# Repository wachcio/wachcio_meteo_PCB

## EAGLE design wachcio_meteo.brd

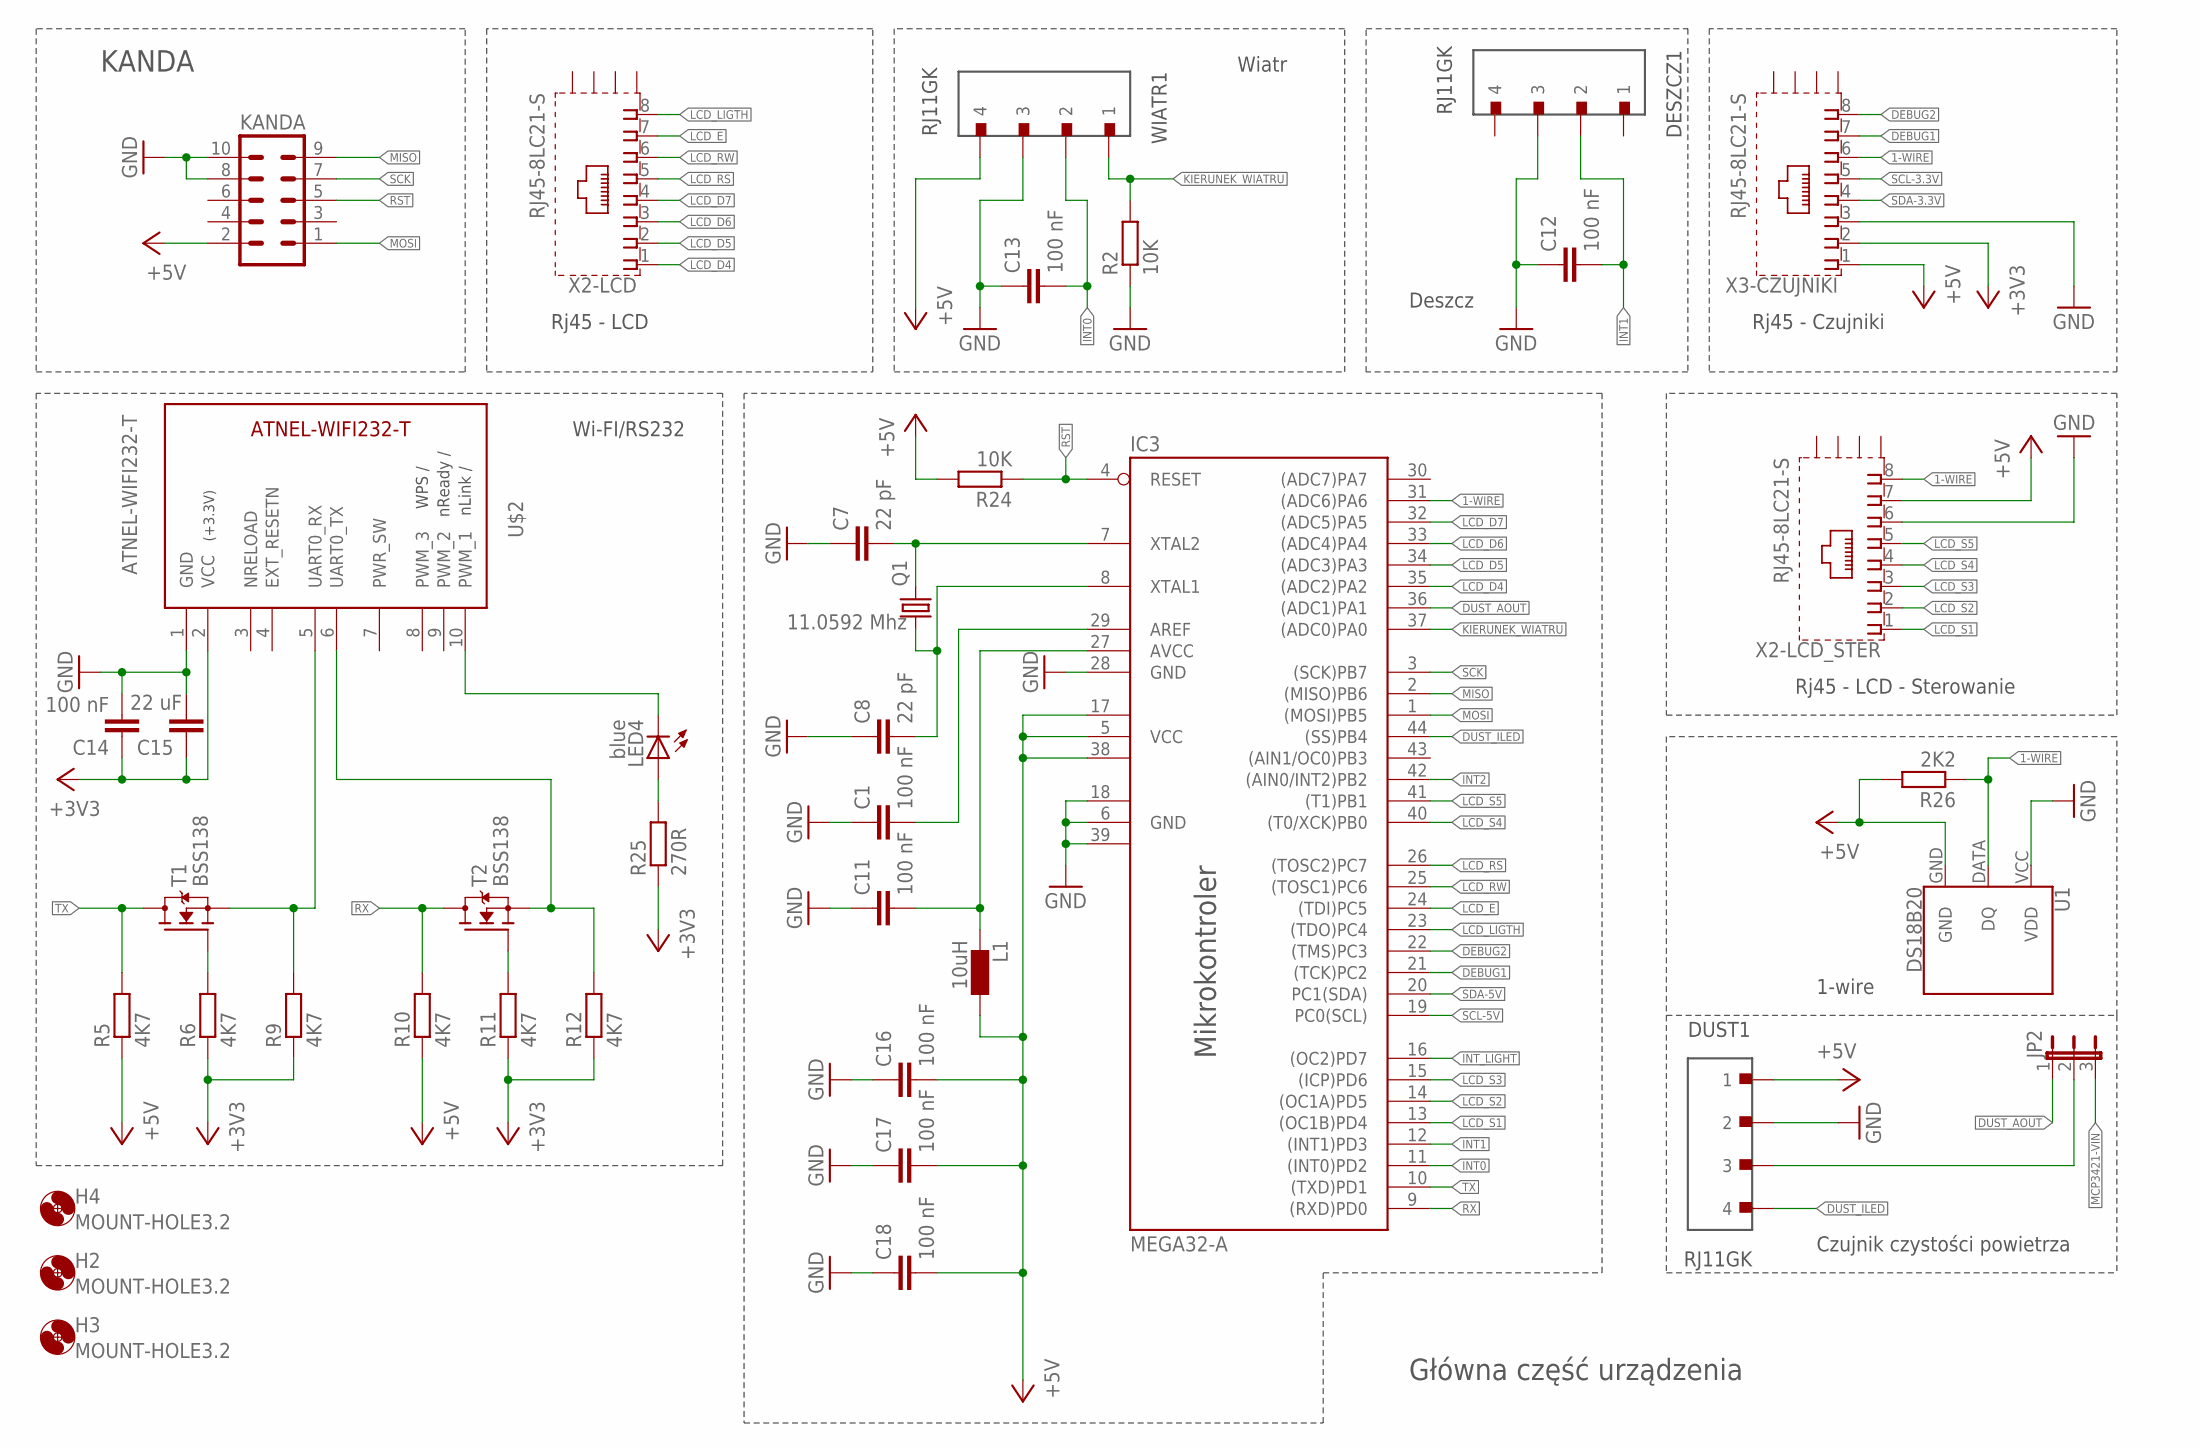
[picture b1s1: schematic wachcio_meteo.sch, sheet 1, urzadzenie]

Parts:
C1, C11, C12, C13, C14, C16, C17, C18: 100 nF; C0805
C7, C8: 22 pF; C0805
C15: 22 uF; C0805
DESZCZ1: RJ11GK
DUST1: RJ11GK
H2, H3, H4: MOUNT-HOLE3.2; 3,2
IC3: MEGA32-A; TQFP44
JP2: JP2E; JP2
KANDA: ML10
L1: 10uH; L3230M
LED4: blue; CHIPLED_1206
Q1: 11.0592 Mhz; SM49
R2, R24: 10K; M0805
R5, R6, R9, R10, R11, R12: 4K7; M0805
R25: 270R; M0805
R26: 2K2; M0805
T1, T2: BSS138; SOT23
U1: DS18B20; TO-92-AMMO
U$2: ATNEL-WIFI232-T
WIATR1: RJ11GK
X2-LCD, X2-LCD_STER, X3-CZUJNIKI: RJ45-8LC21-S; RJ45-SHIELD1

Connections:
1-WIRE: IC3.31 ((ADC6)PA6), R26.1, U1.DATA (DQ), X2-LCD_STER.8, X3-CZUJNIKI.6
+3V3: C14.1, C15.1, R6.1, R9.1, R11.1, R12.1, R25.1, U$2.2 (VCC), X3-CZUJNIKI.2; also elsewhere on the board
+5V: C16.2, C17.2, C18.2, DUST1.1, IC3.5 (VCC), IC3.17 (VCC1), IC3.38 (VCC2), KANDA.2, L1.1, R5.1, R10.1, R24.2, R26.2, U1.GND, WIATR1.4, X2-LCD_STER.7, X3-CZUJNIKI.1; also elsewhere on the board
DEBUG1: IC3.21 ((TCK)PC2), X3-CZUJNIKI.7; also elsewhere on the board
DEBUG2: IC3.22 ((TMS)PC3), X3-CZUJNIKI.8; also elsewhere on the board
DUST_AOUT: IC3.36 ((ADC1)PA1), JP2.1
DUST_ILED: DUST1.4, IC3.44 ((SS)PB4)
GND: C1.1, C7.1, C8.1, C11.1, C12.1, C13.1, C14.2, C15.2, C16.1, C17.1, C18.1, DESZCZ1.3, DUST1.2, IC3.6 (GND), IC3.18 (GND1), IC3.28 (GND), IC3.39 (GND2), KANDA.8, KANDA.10, R2.1, U1.VCC (VDD), U$2.1 (GND), WIATR1.3, X2-LCD_STER.6, X3-CZUJNIKI.3; also elsewhere on the board
INT0: C13.2, IC3.11 ((INT0)PD2), WIATR1.2
INT1: C12.2, DESZCZ1.2, IC3.12 ((INT1)PD3)
INT2: IC3.42 ((AIN0/INT2)PB2); also elsewhere on the board
INT_LIGHT: IC3.16 ((OC2)PD7); also elsewhere on the board
KIERUNEK_WIATRU: IC3.37 ((ADC0)PA0), R2.2, WIATR1.1
LCD_D4: IC3.35 ((ADC2)PA2), X2-LCD.1
LCD_D5: IC3.34 ((ADC3)PA3), X2-LCD.2
LCD_D6: IC3.33 ((ADC4)PA4), X2-LCD.3
LCD_D7: IC3.32 ((ADC5)PA5), X2-LCD.4
LCD_E: IC3.24 ((TDI)PC5), X2-LCD.7
LCD_LIGTH: IC3.23 ((TDO)PC4), X2-LCD.8
LCD_RS: IC3.26 ((TOSC2)PC7), X2-LCD.5
LCD_RW: IC3.25 ((TOSC1)PC6), X2-LCD.6
LCD_S1: IC3.13 ((OC1B)PD4), X2-LCD_STER.1
LCD_S2: IC3.14 ((OC1A)PD5), X2-LCD_STER.2
LCD_S3: IC3.15 ((ICP)PD6), X2-LCD_STER.3
LCD_S4: IC3.40 ((T0/XCK)PB0), X2-LCD_STER.4
LCD_S5: IC3.41 ((T1)PB1), X2-LCD_STER.5
MCP3421-VIN: JP2.3; also elsewhere on the board
MISO: IC3.2 ((MISO)PB6), KANDA.9
MOSI: IC3.1 ((MOSI)PB5), KANDA.1
unnamed: R9.2, T1.2 (S), U$2.5 (UART0_RX)
unnamed: C11.2, IC3.27 (AVCC), L1.2
unnamed: C1.2, IC3.29 (AREF)
unnamed: LED4.A, R25.2
unnamed: R6.2, T1.1 (G)
unnamed: LED4.C, U$2.10 (PWM_1)
unnamed: R12.2, T2.2 (S), U$2.6 (UART0_TX)
unnamed: C7.2, IC3.7 (XTAL2), Q1.2
unnamed: C8.2, IC3.8 (XTAL1), Q1.1
unnamed: DUST1.3, JP2.2
unnamed: R11.2, T2.1 (G)
RST: IC3.4 (RESET), KANDA.5, R24.1
RX: IC3.9 ((RXD)PD0), R10.2, T2.3 (D)
SCK: IC3.3 ((SCK)PB7), KANDA.7
SCL-3.3V: X3-CZUJNIKI.5; also elsewhere on the board
SCL-5V: IC3.19 (PC0(SCL)); also elsewhere on the board
SDA-3.3V: X3-CZUJNIKI.4; also elsewhere on the board
SDA-5V: IC3.20 (PC1(SDA)); also elsewhere on the board
TX: IC3.10 ((TXD)PD1), R5.2, T1.3 (D)

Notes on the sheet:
KANDA
Mikrokontroler
Rj45 - LCD
Wiatr
Deszcz
Rj45 - Czujniki
Wi-FI/RS232
1-wire
Rj45 - LCD - Sterowanie
Główna część urządzenia
Czujnik czystości powietrza

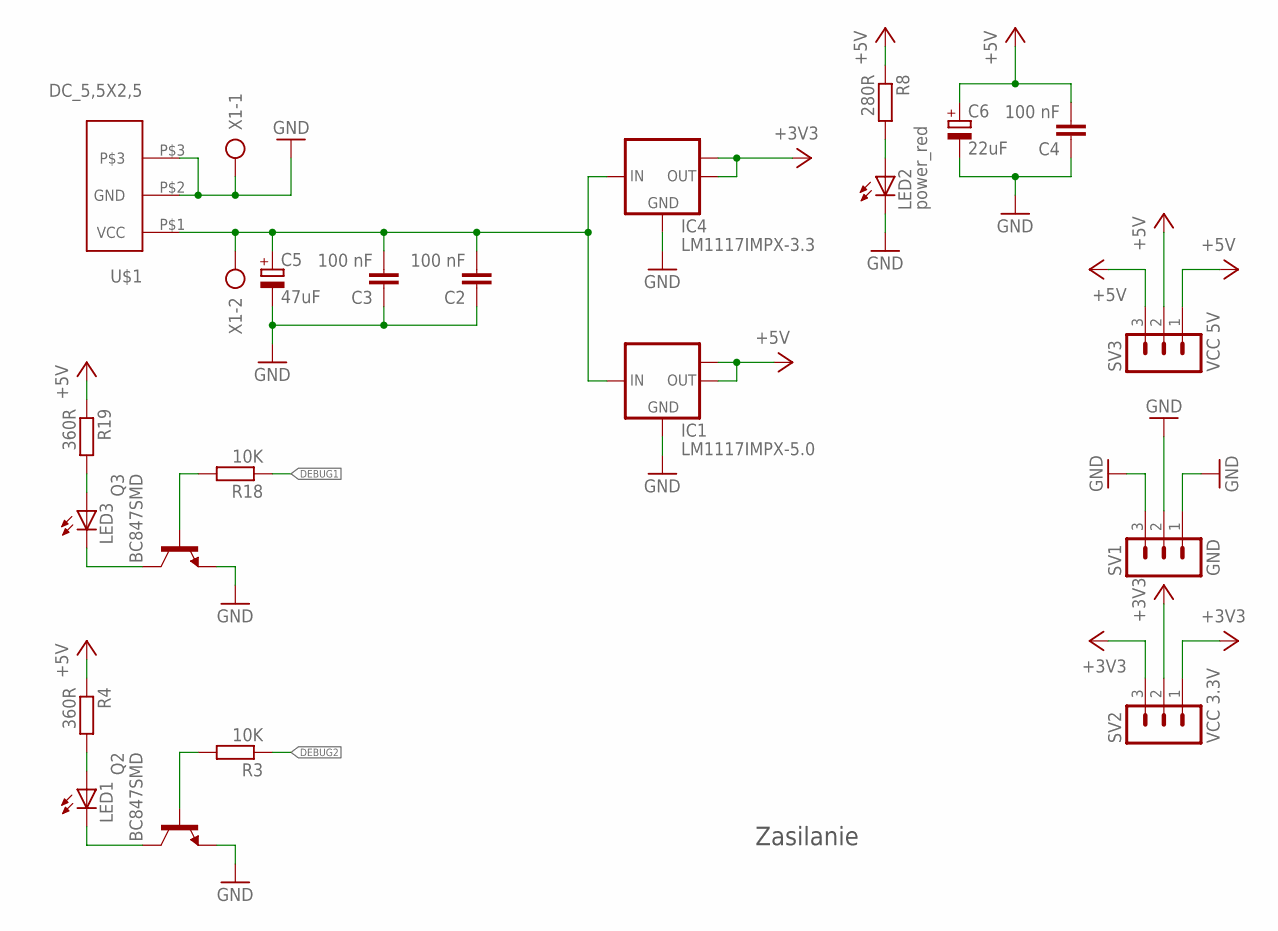
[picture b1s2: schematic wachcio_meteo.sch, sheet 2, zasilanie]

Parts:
C2, C3, C4: 100 nF; C0805
C5: 47uF; B45181A
C6: 22uF; B45181A
IC1: LM1117IMPX-5.0; SOT223
IC4: LM1117IMPX-3.3; SOT223
LED1, LED3: LED3MM
LED2: power_red; CHIPLED_1206
Q2, Q3: BC847SMD; SOT23
R3, R18: 10K; M0805
R4, R19: 360R; M0805
R8: 280R; M0805
SV1: GND; MA03-1
SV2: VCC 3.3V; MA03-1
SV3: VCC 5V; MA03-1
U$1: DC_5,5X2,5
X1: AK500/2

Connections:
+3V3: IC4.2 (OUT), IC4.TAB (OUT1), SV2.1, SV2.2, SV2.3; also elsewhere on the board
+5V: C4.2, C6.+, IC1.2 (OUT), IC1.TAB (OUT1), R4.1, R8.1, R19.1, SV3.1, SV3.2, SV3.3; also elsewhere on the board
+9V: C2.2, C3.2, C5.+, IC1.3 (IN), IC4.3 (IN), U$1.P$1 (VCC), X1.2
DEBUG1: R18.1; also elsewhere on the board
DEBUG2: R3.1; also elsewhere on the board
GND: C2.1, C3.1, C4.1, C5.-, C6.-, IC1.1 (GND), IC4.1 (GND), LED2.C, Q2.2 (E), Q3.2 (E), SV1.1, SV1.2, SV1.3, U$1.P$2 (GND), U$1.P$3, X1.1; also elsewhere on the board
unnamed: Q2.1 (B), R3.2
unnamed: LED2.A, R8.2
unnamed: LED1.K (C), Q2.3 (C)
unnamed: LED1.A, R4.2
unnamed: Q3.1 (B), R18.2
unnamed: LED3.K (C), Q3.3 (C)
unnamed: LED3.A, R19.2

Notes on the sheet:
Zasilanie

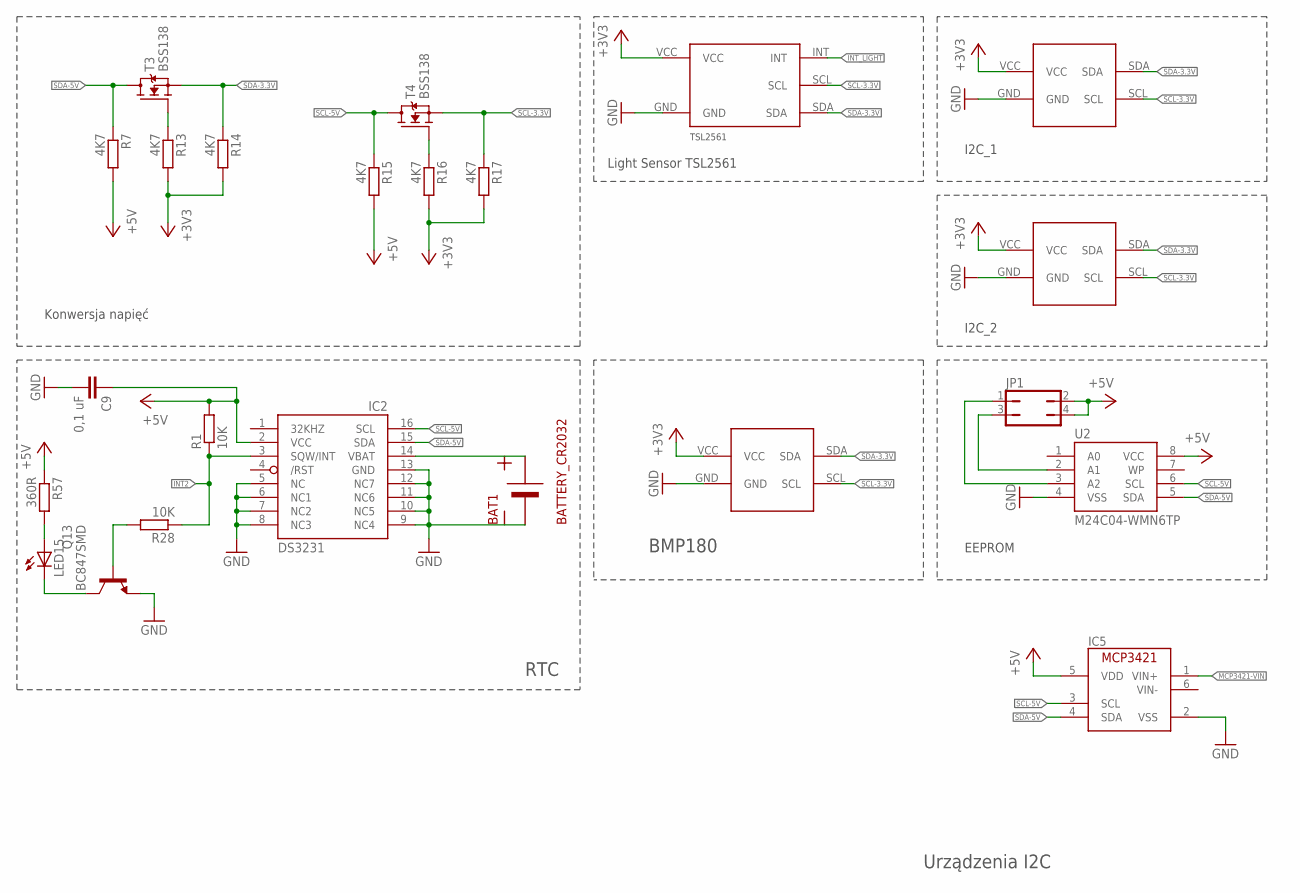
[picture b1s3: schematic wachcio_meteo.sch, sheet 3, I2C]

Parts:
BAT1: BATTERY_CR2032
C9: 0,1 uF; C0805
IC2: DS3231/SO; SO16W
IC5: MCP3421; SOT-23
JP1: JP2Q
LED15: LED3MM
Q13: BC847SMD; SOT23
R1, R28: 10K; M0805
R7, R13, R14, R15, R16, R17: 4K7; M0805
R57: 360R; M0805
T3, T4: BSS138; SOT23
U2: M24C04-WMN6TP; SO08
U$3: BMP180
U$5, U$6: I2C_BOARD
U$7: TSL2561GY-2561; TSL2561

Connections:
+3V3: R13.2, R14.2, R16.2, R17.2, U$3.VCC, U$5.VCC, U$6.VCC, U$7.VCC; also elsewhere on the board
+5V: C9.1, IC2.2 (VCC), IC5.5 (VDD), JP1.2, JP1.4, R1.2, R7.2, R15.2, R57.1, U2.8 (VCC); also elsewhere on the board
GND: BAT1.-, C9.2, IC2.5 (NC), IC2.6 (NC1), IC2.7 (NC2), IC2.8 (NC3), IC2.9 (NC4), IC2.10 (NC5), IC2.11 (NC6), IC2.12 (NC7), IC2.13 (GND), IC5.2 (VSS), Q13.2 (E), U2.4 (VSS), U$3.GND, U$5.GND, U$6.GND, U$7.GND; also elsewhere on the board
INT2: IC2.3 (SQW/INT), R1.1, R28.1; also elsewhere on the board
INT_LIGHT: U$7.INT; also elsewhere on the board
MCP3421-VIN: IC5.1 (VIN+); also elsewhere on the board
unnamed: BAT1.+, IC2.14 (VBAT)
unnamed: R13.1, T3.1 (G)
unnamed: R16.1, T4.1 (G)
unnamed: JP1.3, U2.2 (A1)
unnamed: JP1.1, U2.3 (A2)
unnamed: Q13.1 (B), R28.2
unnamed: LED15.K (C), Q13.3 (C)
unnamed: LED15.A, R57.2
SCL-3.3V: R17.1, T4.2 (S), U$3.SCL, U$5.SCL, U$6.SCL, U$7.SCL; also elsewhere on the board
SCL-5V: IC2.16 (SCL), IC5.3 (SCL), R15.1, T4.3 (D), U2.6 (SCL); also elsewhere on the board
SDA-3.3V: R14.1, T3.2 (S), U$3.SDA, U$5.SDA, U$6.SDA, U$7.SDA; also elsewhere on the board
SDA-5V: IC2.15 (SDA), IC5.4 (SDA), R7.1, T3.3 (D), U2.5 (SDA); also elsewhere on the board

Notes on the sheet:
Konwersja napięć
RTC
BMP180
I2C_1
I2C_2
EEPROM
Light Sensor TSL2561
Urządzenia I2C

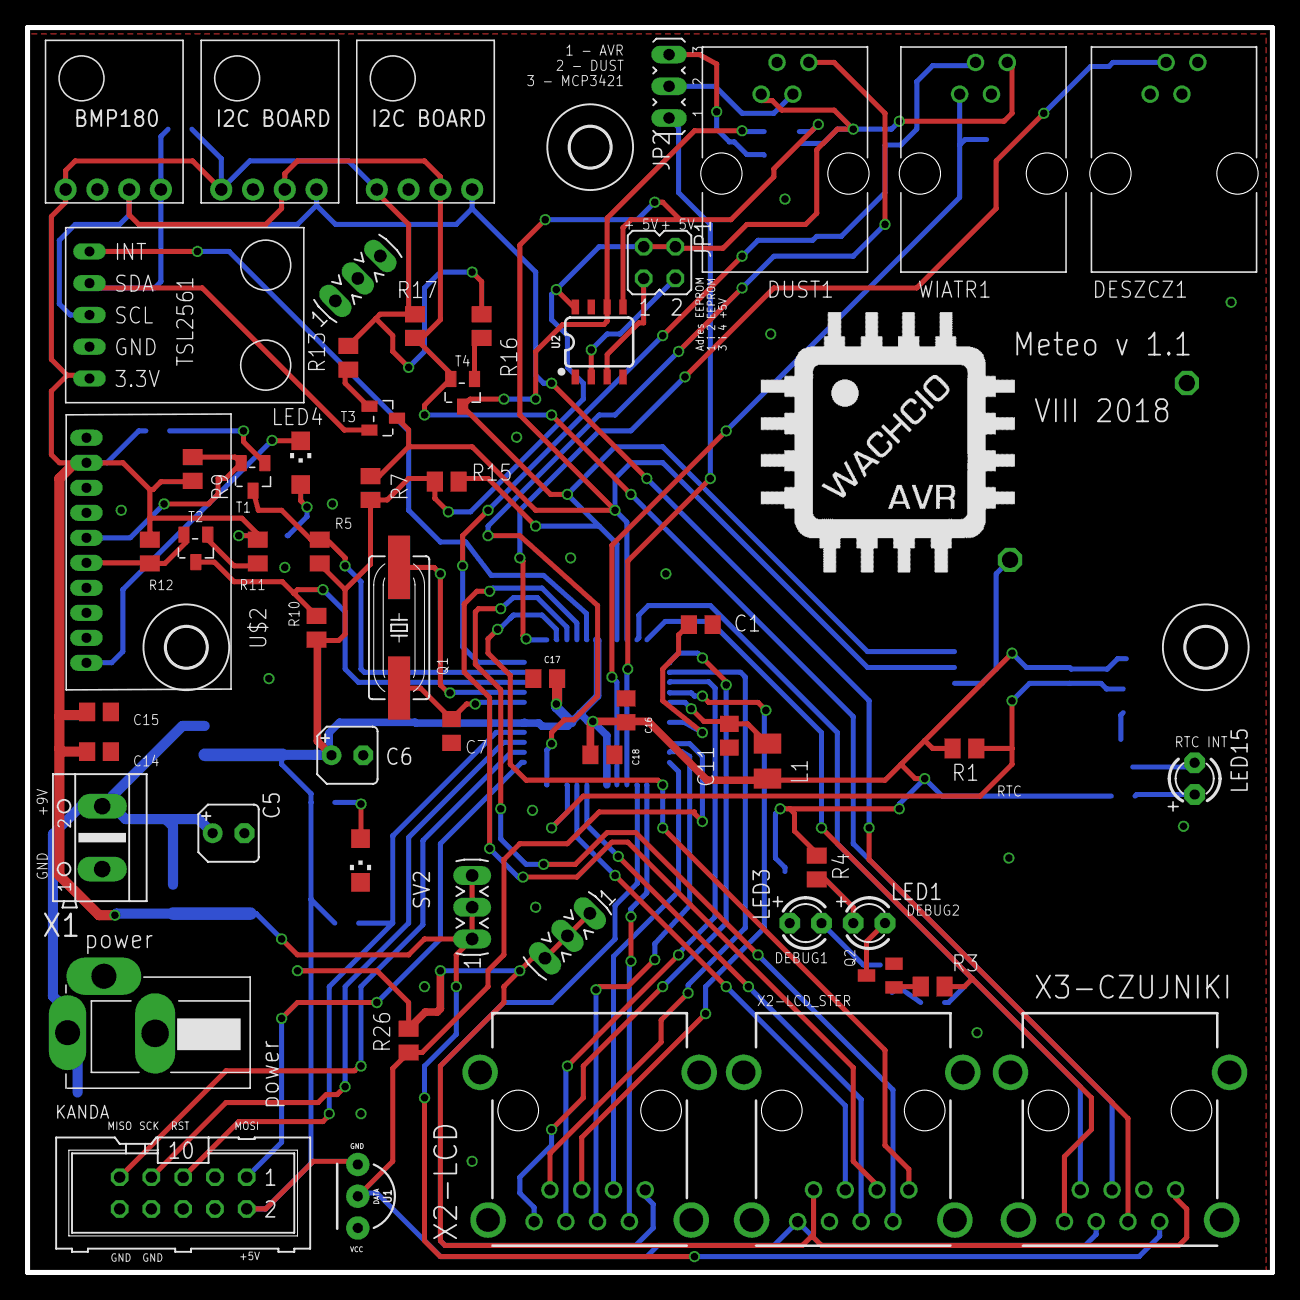
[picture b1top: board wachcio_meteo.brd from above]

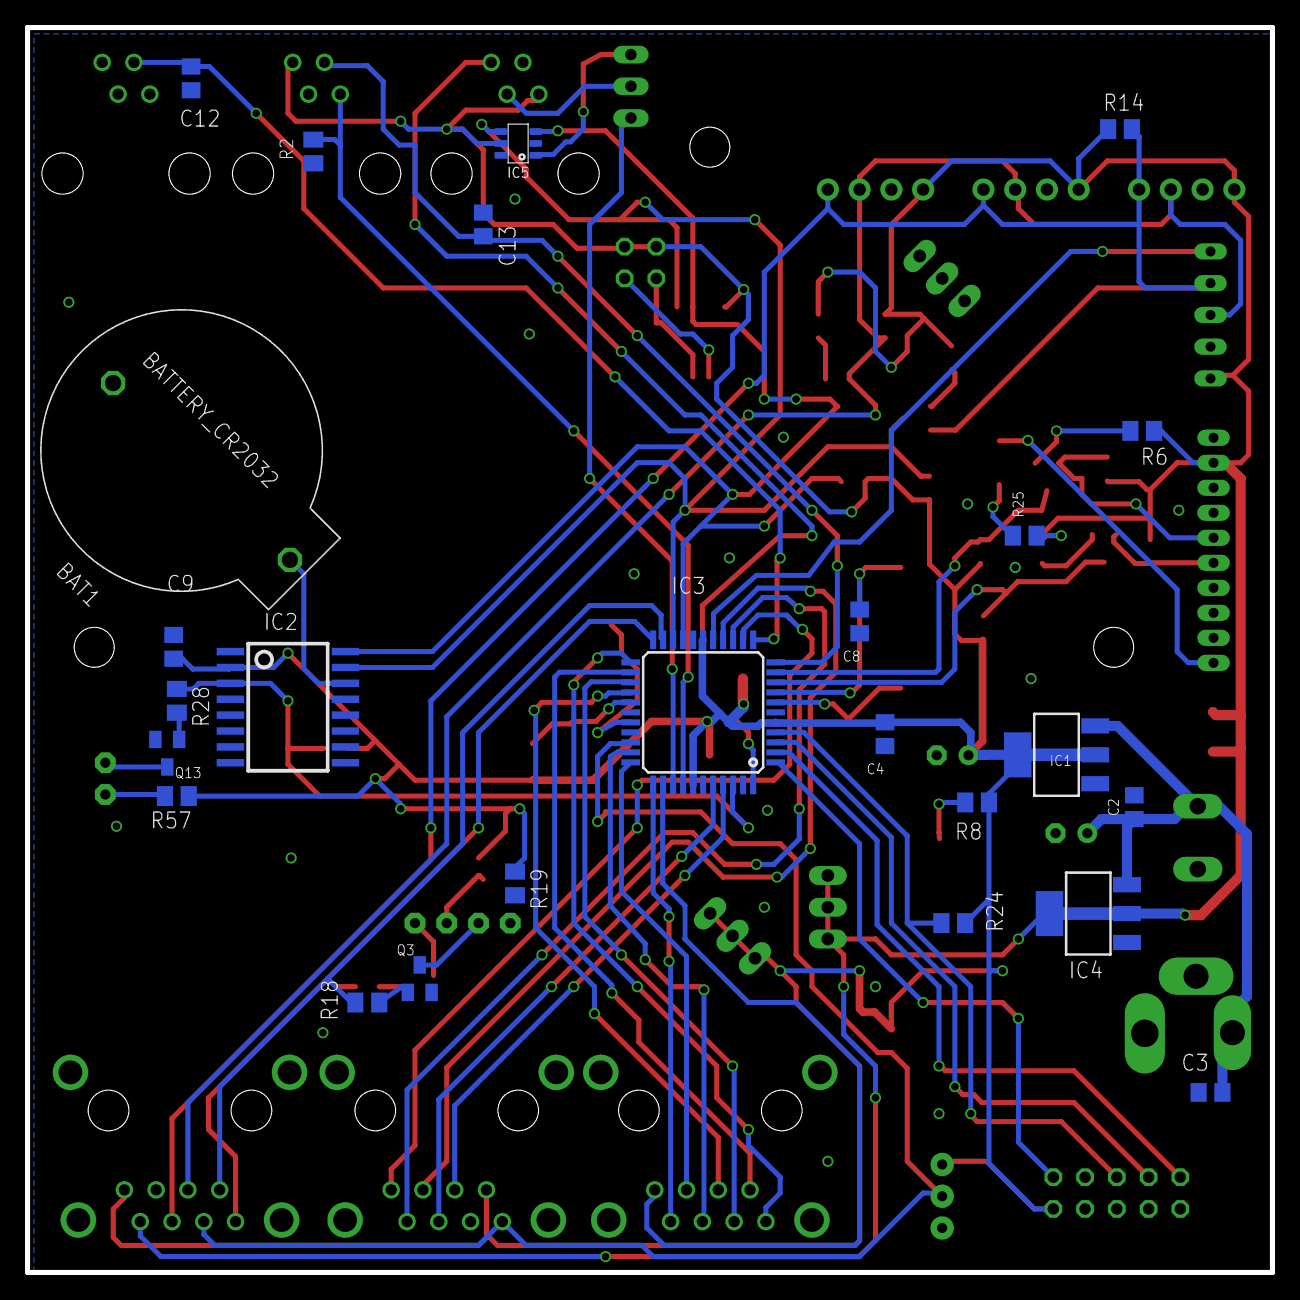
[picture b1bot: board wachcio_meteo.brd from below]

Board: 2 copper layers, 99.6 x 99.6 mm, 86 parts (25 on the bottom side), 64 nets.

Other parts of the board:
U$8: LOGO

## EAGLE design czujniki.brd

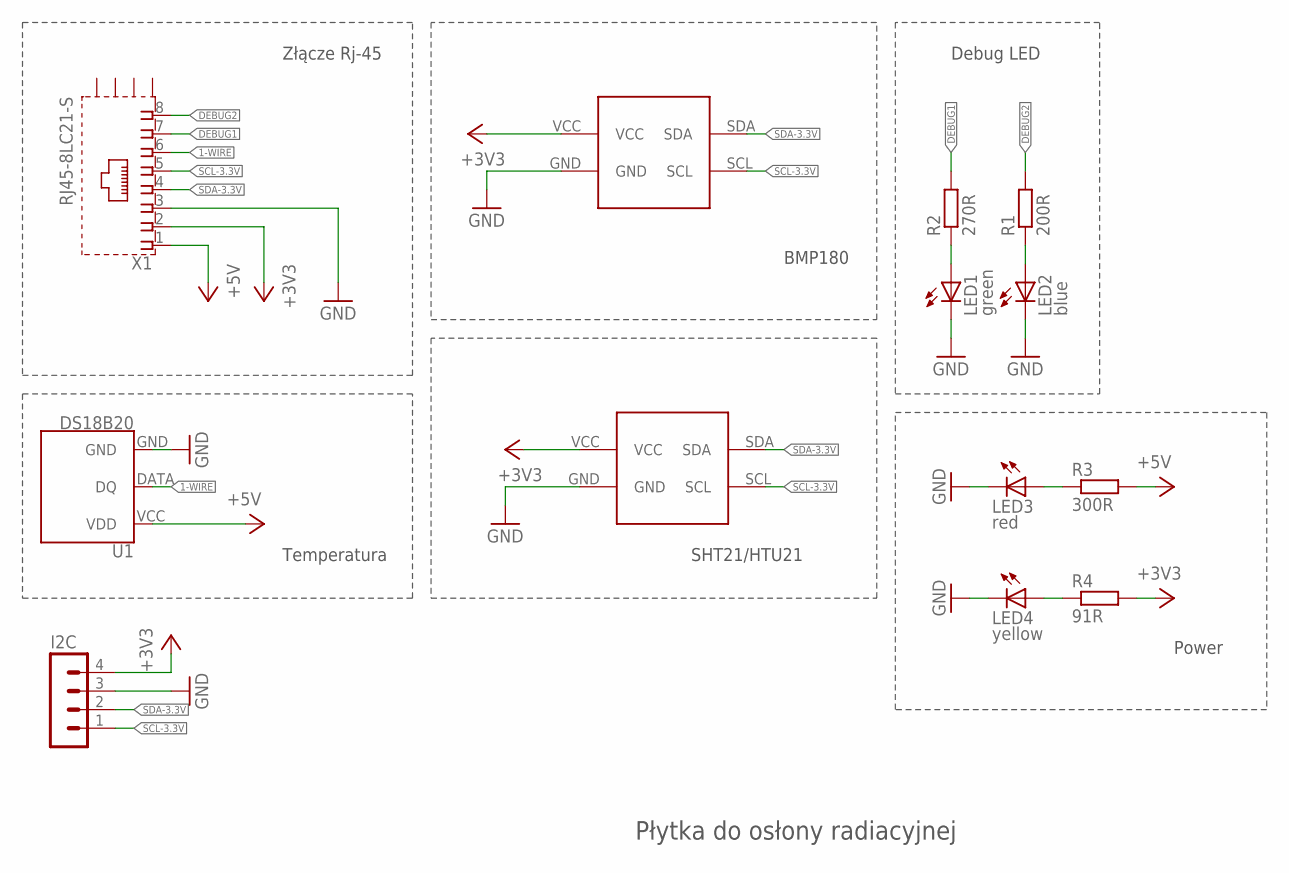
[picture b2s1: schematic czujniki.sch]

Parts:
I2C: MA04-1
LED1: green; CHIPLED_1206
LED2: blue; CHIPLED_1206
LED3: red; CHIPLED_1206
LED4: yellow; CHIPLED_1206
R1: 200R; M0805
R2: 270R; M0805
R3: 300R; M0805
R4: 91R; M0805
U1: DS18B20; TO-92-AMMO
U$1: BMP180
U$2: I2C_BOARD
X1: RJ45-8LC21-S; RJ45-SHIELD1

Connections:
1-WIRE: U1.DATA (DQ), X1.6
+3V3: I2C.4, R4.2, U$1.VCC, U$2.VCC, X1.2
+5V: R3.2, U1.VCC (VDD), X1.1
DEBUG1: R2.2, X1.7
DEBUG2: R1.2, X1.8
GND: I2C.3, LED1.C, LED2.C, LED3.C, LED4.C, U1.GND, U$1.GND, U$2.GND, X1.3
unnamed: LED1.A, R2.1
unnamed: LED2.A, R1.1
unnamed: LED3.A, R3.1
unnamed: LED4.A, R4.1
SCL-3.3V: I2C.1, U$1.SCL, U$2.SCL, X1.5
SDA-3.3V: I2C.2, U$1.SDA, U$2.SDA, X1.4

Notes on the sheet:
BMP180
SHT21/HTU21
Złącze Rj-45
Temperatura
Debug LED
Płytka do osłony radiacyjnej
Power

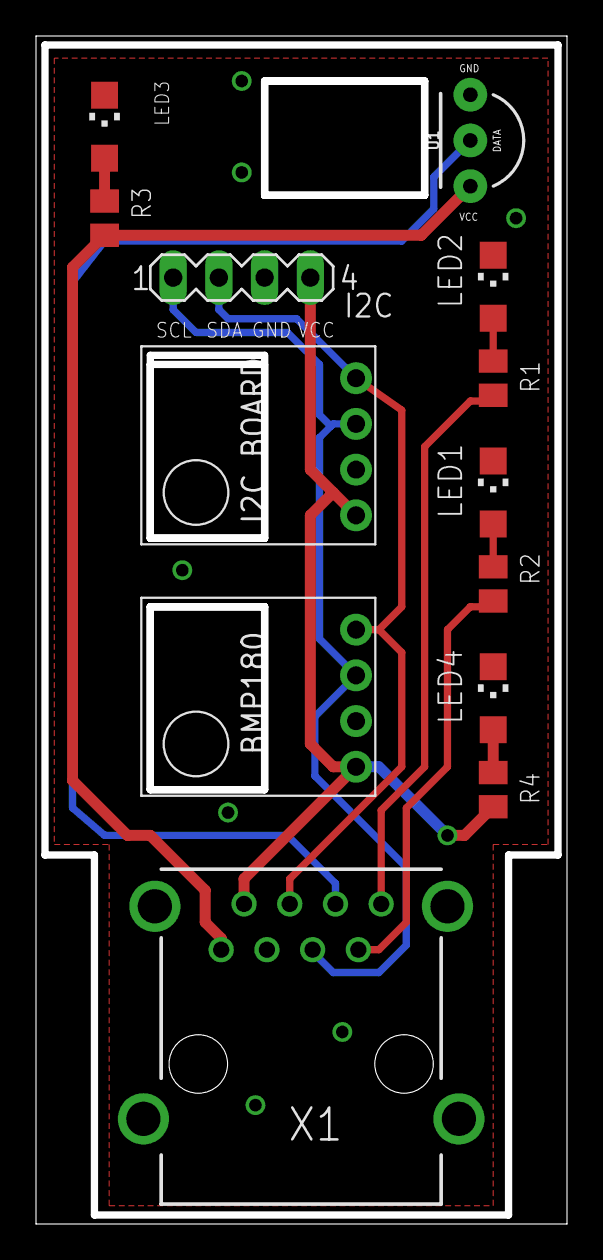
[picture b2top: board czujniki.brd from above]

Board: 2 copper layers, 29.5 x 66.0 mm, 13 parts (0 on the bottom side), 12 nets.

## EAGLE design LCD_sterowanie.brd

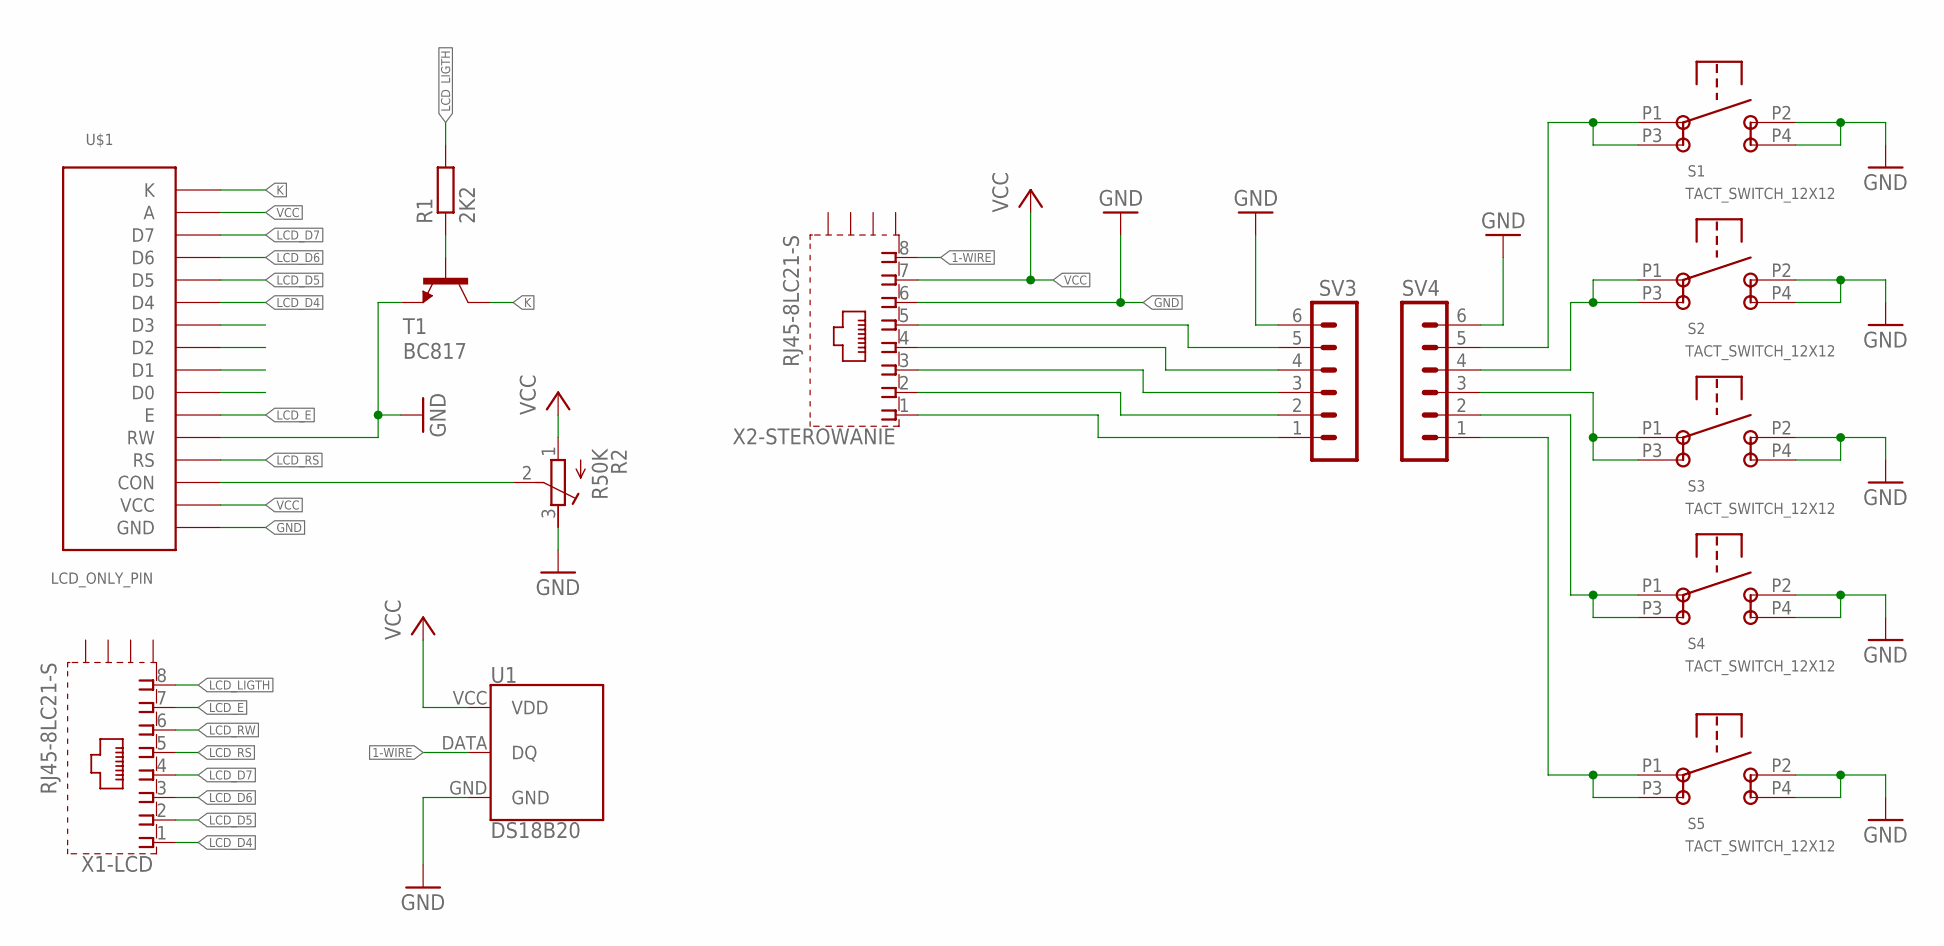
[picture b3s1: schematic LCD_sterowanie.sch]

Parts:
R1: 2K2; M0805
R2: R50K; RTRIM3296P
S1, S2, S3, S4, S5: TACT_SWITCH_12X12
SV3, SV4: MA06-1
T1: BC817; SOT23
U1: DS18B20; TO-92-AMMO
U$1: LCD_ONLY_PIN
X1-LCD, X2-STEROWANIE: RJ45-8LC21-S; RJ45-SHIELD1

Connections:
1-WIRE: U1.DATA (DQ), X2-STEROWANIE.8
GND: R2.3 (E), S1.P2, S1.P4, S2.P2, S2.P4, S3.P2, S3.P4, S4.P2, S4.P4, S5.P2, S5.P4, SV3.6, SV4.6, T1.2 (E), U1.GND, U$1.GND, U$1.RW, X2-STEROWANIE.6
K: T1.3 (C), U$1.K
LCD_D4: U$1.D4, X1-LCD.1
LCD_D5: U$1.D5, X1-LCD.2
LCD_D6: U$1.D6, X1-LCD.3
LCD_D7: U$1.D7, X1-LCD.4
LCD_E: U$1.E, X1-LCD.7
LCD_LIGTH: R1.2, X1-LCD.8
LCD_RS: U$1.RS, X1-LCD.5
LCD_RW: X1-LCD.6
unnamed: R1.1, T1.1 (B)
unnamed: S1.P1, S1.P3, SV4.5
unnamed: S2.P1, S2.P3, SV4.4
unnamed: S3.P1, S3.P3, SV4.3
unnamed: S4.P1, S4.P3, SV4.2
unnamed: S5.P1, S5.P3, SV4.1
unnamed: R2.2 (S), U$1.CON
S1: SV3.1, X2-STEROWANIE.1
S2: SV3.2, X2-STEROWANIE.2
S3: SV3.3, X2-STEROWANIE.3
S4: SV3.4, X2-STEROWANIE.4
S5: SV3.5, X2-STEROWANIE.5
VCC: R2.1 (A), U1.VCC (VDD), U$1.A, U$1.VCC, X2-STEROWANIE.7

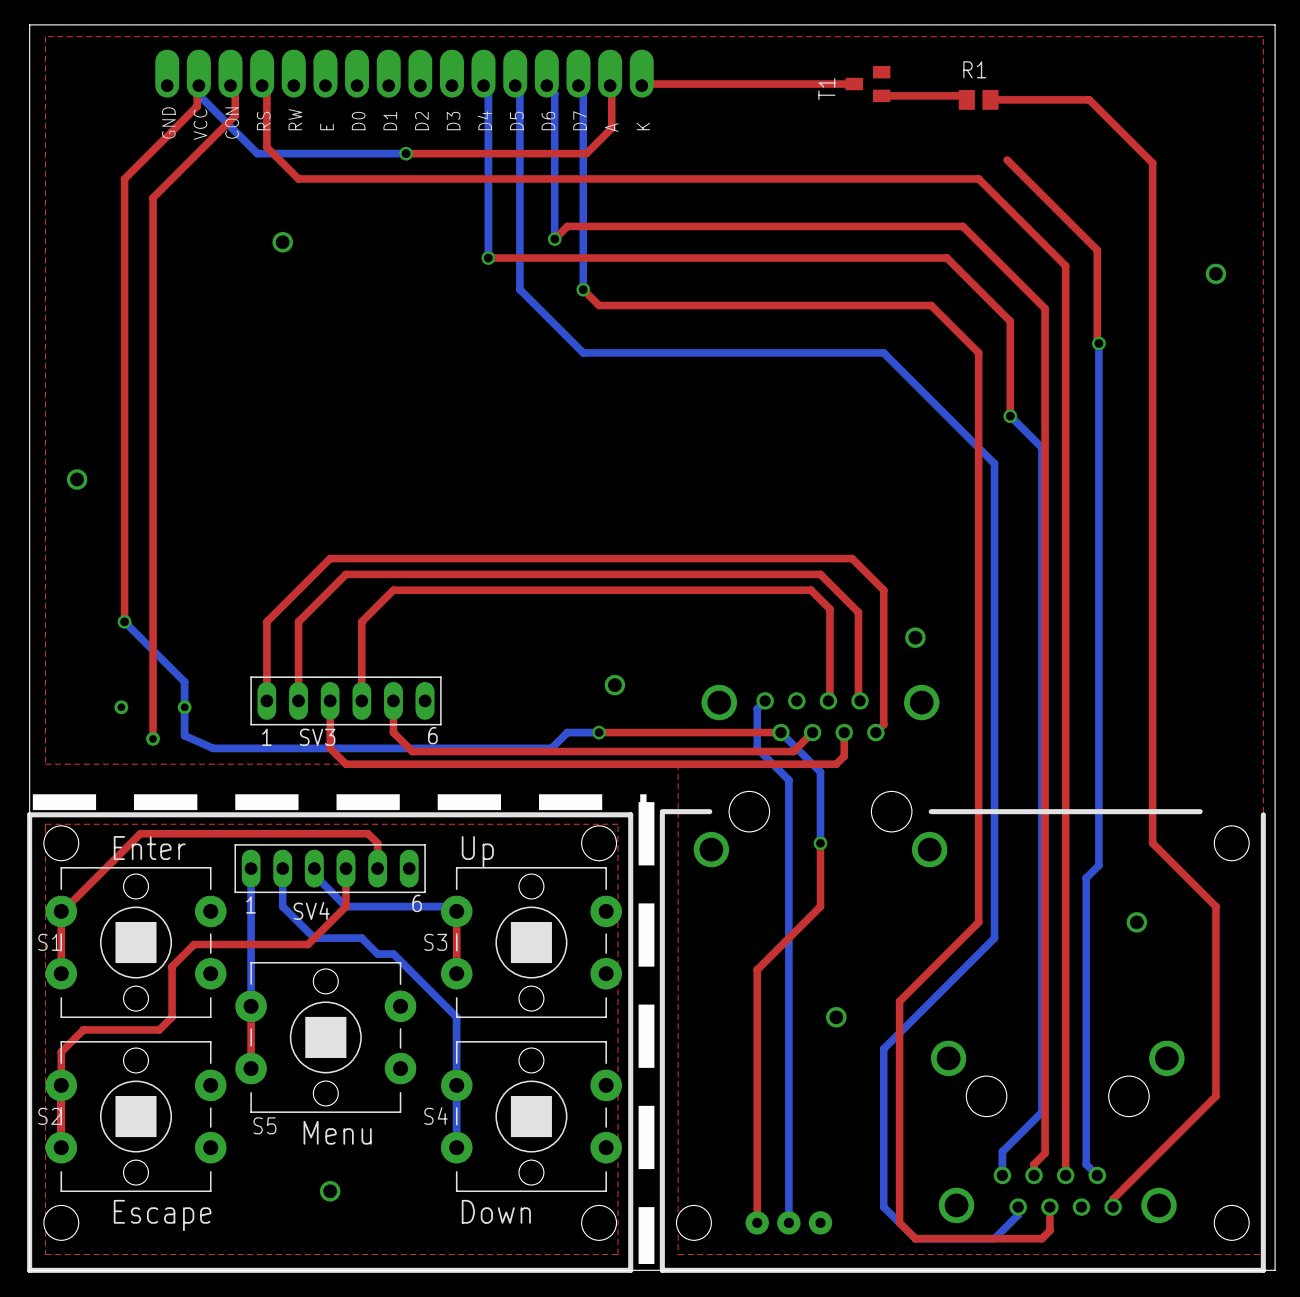
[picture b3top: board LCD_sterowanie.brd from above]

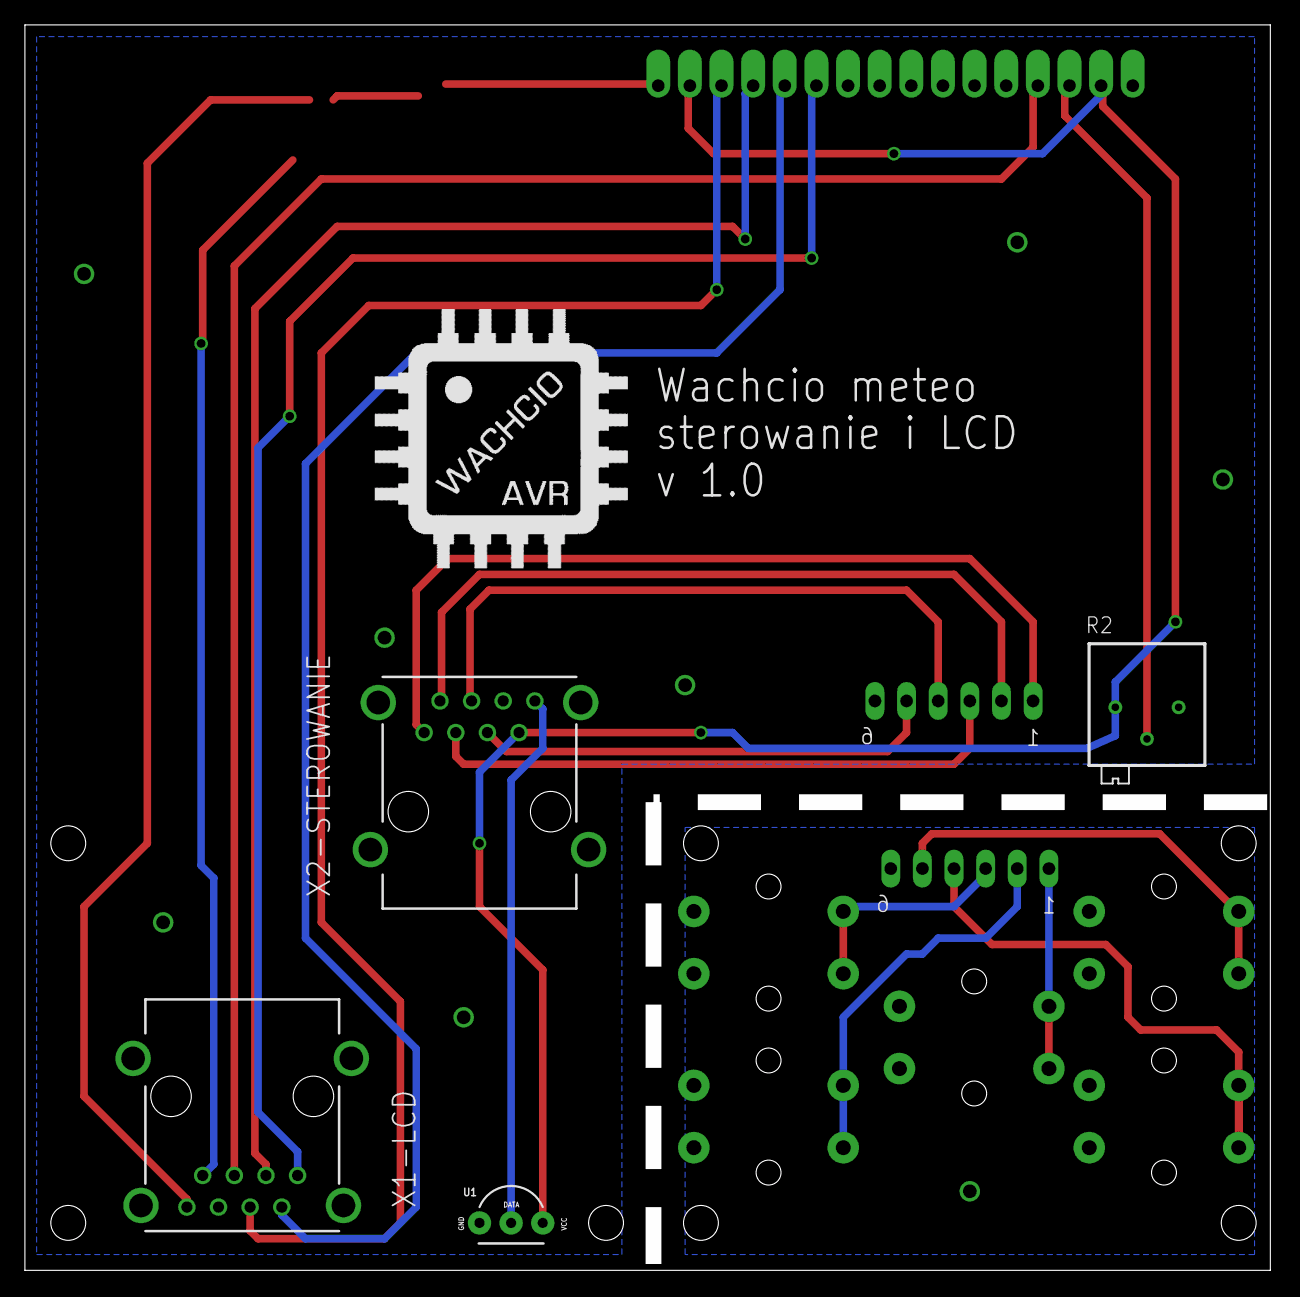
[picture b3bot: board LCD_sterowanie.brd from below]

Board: 2 copper layers, 100.0 x 100.0 mm, 15 parts (5 on the bottom side), 23 nets.

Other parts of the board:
U$2: LOGO

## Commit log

2018-09-21 Add image files - render PCB-s

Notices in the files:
parts and their libraries:
SparkFun-Sensors: Licensing: Creative Commons ShareAlike 4.0 International - https://creativecommons.org/licenses/by-sa/4.0
FaBo-Sensor: Released under the Creative Commons Attribution-ShareAlike 4.0 License
https://creativecommons.org/licenses/by-sa/4.0
